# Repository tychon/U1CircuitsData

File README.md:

# U1CircuitsData

Code for data analysis and simulations accompanying the publication [arXiv:2108.01086](https://arxiv.org/abs/2108.01086).

Clone repository and run notebooks in your own Jupyter instance or click binder button above to run on other people's computers (aka 'the cloud'). Note that most computations take rather long on the public BinderHub infrastructure and are best performed locally.

  * `MM-DD`: folders with raw data, named by date in 2021.
  * `U1 Simulations.ipynb`: Numerical simulations. Produces files for `U1 Figures.ipynb` too.
  * `U1 Figures.ipynb`: Data analysis for Figures appearing in paper.
  * `KiCad_U1-block/`: Schematic and PCB design.
  * `redpitaya-measurements/`: Measurement scripts used with Red Pitaya.

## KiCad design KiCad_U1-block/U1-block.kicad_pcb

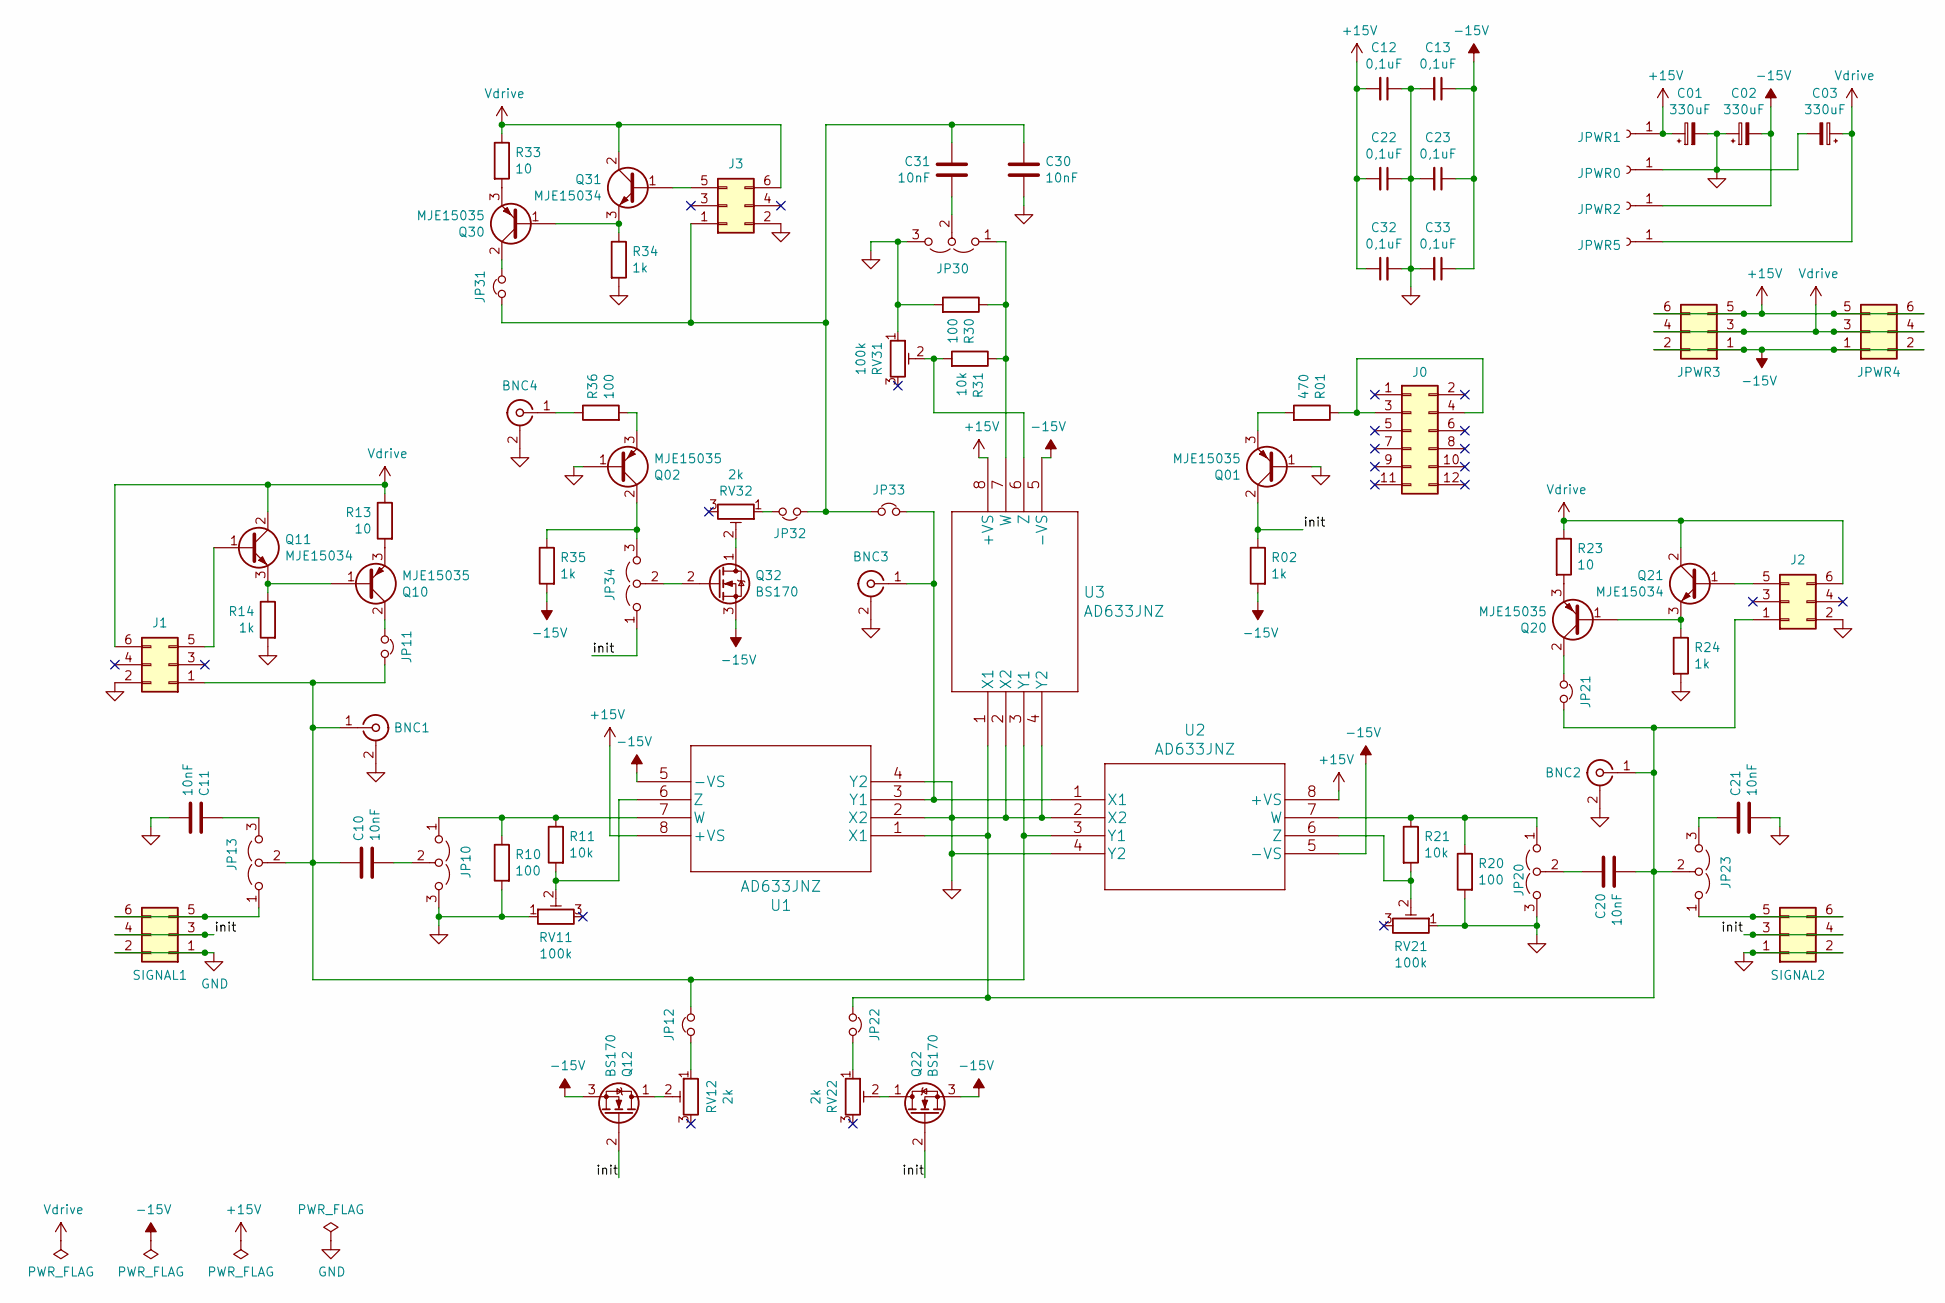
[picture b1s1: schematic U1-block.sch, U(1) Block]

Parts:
BNC1, BNC2, BNC3, BNC4: Conn_Coaxial; BNC_Amphenol_B6252HB-NPP3G-50_Horizontal
C01, C02, C03: 330uF; CP_Radial_D10.0mm_P5.00mm
C10, C11, C20, C21, C30, C31: 10nF; C_Rect_L7.2mm_W7.2mm_P5.00mm_FKS2_FKP2_MKS2_MKP2
C12, C13, C22, C23, C32, C33: 0,1uF; C_Disc_D5.1mm_W3.2mm_P5.00mm
J0: Conn_02x06_Counter_Clockwise; PinSocket_2x06_P2.54mm_Horizontal
J1, J2, J3: Conn_02x03_Odd_Even; PinSocket_2x03_P2.54mm_Horizontal
JP10, JP13, JP20, JP23, JP30, JP34: Jumper_3_Open; PinSocket_1x03_P2.54mm_Vertical
JP11, JP12, JP21, JP22, JP31, JP32, JP33: Jumper_NC_Small; PinHeader_1x02_P2.54mm_Vertical
JPWR0, JPWR1, JPWR2, JPWR5: Conn_01x01_Female; Banana Mini Jack
JPWR3: Conn_02x03_Odd_Even; PinHeader_2x03_P2.54mm_Horizontal
JPWR4: Conn_02x03_Odd_Even; PinSocket_2x03_P2.54mm_Horizontal
Q01, Q02, Q10, Q20, Q30: MJE15035; TO-220-3_Vertical
Q11, Q21, Q31: MJE15034; TO-220-3_Vertical
Q12, Q22, Q32: BS170; TO-92_Inline
R01: 470; R_Axial_DIN0207_L6.3mm_D2.5mm_P7.62mm_Horizontal
R02, R14, R24, R34, R35: 1k; R_Axial_DIN0207_L6.3mm_D2.5mm_P7.62mm_Horizontal
R10, R20, R30, R36: 100; R_Axial_DIN0207_L6.3mm_D2.5mm_P7.62mm_Horizontal
R11, R21, R31: 10k; R_Axial_DIN0207_L6.3mm_D2.5mm_P7.62mm_Horizontal
R13, R23, R33: 10; R_Axial_DIN0207_L6.3mm_D2.5mm_P7.62mm_Horizontal
RV11, RV21, RV31: 100k; Potentiometer_Bourns_3296W_Vertical
RV12, RV22, RV32: 2k; Potentiometer_Bourns_3296W_Vertical
SIGNAL1: Conn_02x03_Odd_Even; PinHeader_2x03_P2.54mm_Horizontal
SIGNAL2: Conn_02x03_Odd_Even; PinSocket_2x03_P2.54mm_Horizontal
U1, U2, U3: AD633JNZ; DIP-8_W7.62mm_Socket_LongPads

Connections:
+15V: C01.1, C12.2, C22.2, C32.1, JPWR1.1, JPWR3.5, JPWR3.6, JPWR4.5, JPWR4.6, U1.8 (+VS), U2.8 (+VS), U3.8 (+VS)
-15V: C02.2, C13.1, C23.1, C33.1, JPWR2.1, JPWR3.1, JPWR3.2, JPWR4.1, JPWR4.2, Q12.3 (S), Q22.3 (S), Q32.3 (S), R02.2, R35.2, U1.5 (-VS), U2.5 (-VS), U3.5 (-VS)
/init: JP34.1 (A), Q01.2 (C), Q12.2 (G), Q22.2 (G), R02.1, SIGNAL1.3, SIGNAL1.4, SIGNAL2.3, SIGNAL2.4
GND: BNC1.2 (Ext), BNC2.2 (Ext), BNC3.2 (Ext), BNC4.2 (Ext), C01.2, C02.1, C03.2, C11.2, C12.1, C13.2, C21.2, C22.1, C23.2, C30.2, C32.2, C33.2, J1.2, J2.2, J3.2, JP10.3 (B), JP20.3 (B), JP30.3 (B), JPWR0.1, Q01.1 (B), Q02.1 (B), R10.2, R14.2, R20.2, R24.2, R30.2, R34.2, RV11.1, RV21.1, RV31.1, SIGNAL1.1, SIGNAL1.2, SIGNAL2.1, SIGNAL2.2, U1.2 (X2), U1.4 (Y2), U2.2 (X2), U2.4 (Y2), U3.2 (X2), U3.4 (Y2)
unnamed: BNC1.1 (In), C10.1, J1.1, JP11.1, JP12.2, JP13.2 (C), U2.3 (Y1), U3.3 (Y1)
unnamed: BNC2.1 (In), C20.2, J2.1, JP21.1, JP22.2, JP23.2 (C), U1.1 (X1), U3.1 (X1)
unnamed: BNC3.1 (In), JP33.2, U1.3 (Y1), U2.1 (X1)
unnamed: BNC4.1 (In), R36.1
unnamed: C10.2, JP10.2 (C)
unnamed: C11.1, JP13.3 (B)
unnamed: C20.1, JP20.2 (C)
unnamed: C21.1, JP23.3 (B)
unnamed: C30.1, C31.1, J3.1, JP31.1, JP32.2, JP33.1
unnamed: C31.2, JP30.2 (C)
unnamed: J0.3, J0.4, R01.1
unnamed: J1.5, Q11.1 (B)
unnamed: J2.5, Q21.1 (B)
unnamed: J3.5, Q31.1 (B)
unnamed: JP10.1 (A), R10.1, R11.1, U1.7 (W)
unnamed: JP11.2, Q10.2 (C)
unnamed: JP12.1, RV12.1
unnamed: JP13.1 (A), SIGNAL1.5, SIGNAL1.6
unnamed: JP20.1 (A), R20.1, R21.1, U2.7 (W)
unnamed: JP21.2, Q20.2 (C)
unnamed: JP22.1, RV22.1
unnamed: JP23.1 (A), SIGNAL2.5, SIGNAL2.6
unnamed: JP30.1 (A), R30.1, R31.1, U3.7 (W)
unnamed: JP31.2, Q30.2 (C)
unnamed: JP32.1, RV32.1
unnamed: JP34.2 (C), Q32.2 (G)
unnamed: JP34.3 (B), Q02.2 (C), R35.1
unnamed: Q01.3 (E), R01.2
unnamed: Q02.3 (E), R36.2
unnamed: Q10.1 (B), Q11.3 (E), R14.1
unnamed: Q10.3 (E), R13.2
unnamed: Q12.1 (D), RV12.2
unnamed: Q20.1 (B), Q21.3 (E), R24.1
unnamed: Q20.3 (E), R23.2
unnamed: Q22.1 (D), RV22.2
unnamed: Q30.1 (B), Q31.3 (E), R34.1
unnamed: Q30.3 (E), R33.2
unnamed: Q32.1 (D), RV32.2
unnamed: R11.2, RV11.2, U1.6 (Z)
unnamed: R21.2, RV21.2, U2.6 (Z)
unnamed: R31.2, RV31.2, U3.6 (Z)
Vdrive: C03.1, J1.6, J2.6, J3.6, JPWR3.3, JPWR3.4, JPWR4.3, JPWR4.4, JPWR5.1, Q11.2 (C), Q21.2 (C), Q31.2 (C), R13.1, R23.1, R33.1

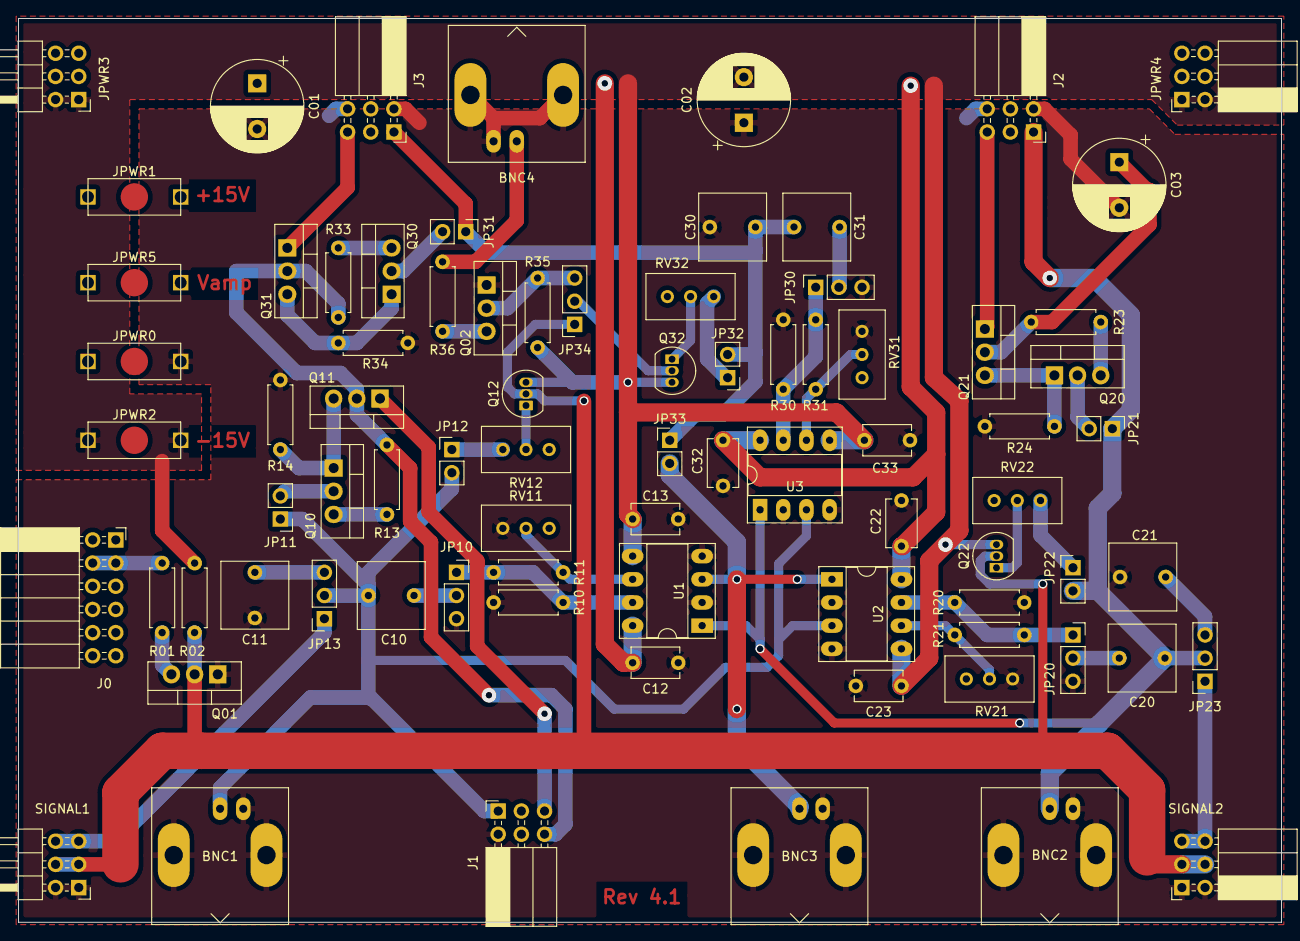
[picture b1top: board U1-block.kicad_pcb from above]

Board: 2 copper layers, 138.4 x 99.1 mm, 80 parts (0 on the bottom side), 46 nets.

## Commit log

2021-08-18 Initial commit with rough code and relevant data files.
2022-01-31 Add KiCad schematics
2022-01-31 Add RedPitaya readout code
2022-01-31 Update Simulations Jupyter notebook
2022-01-31 LICENSE and README
2022-02-02 Update LICENSE
2022-02-03 Rename data files to work in Windows. Code adapted.
2022-05-08 Update figure axis labels to show units in parentheses for PRB
